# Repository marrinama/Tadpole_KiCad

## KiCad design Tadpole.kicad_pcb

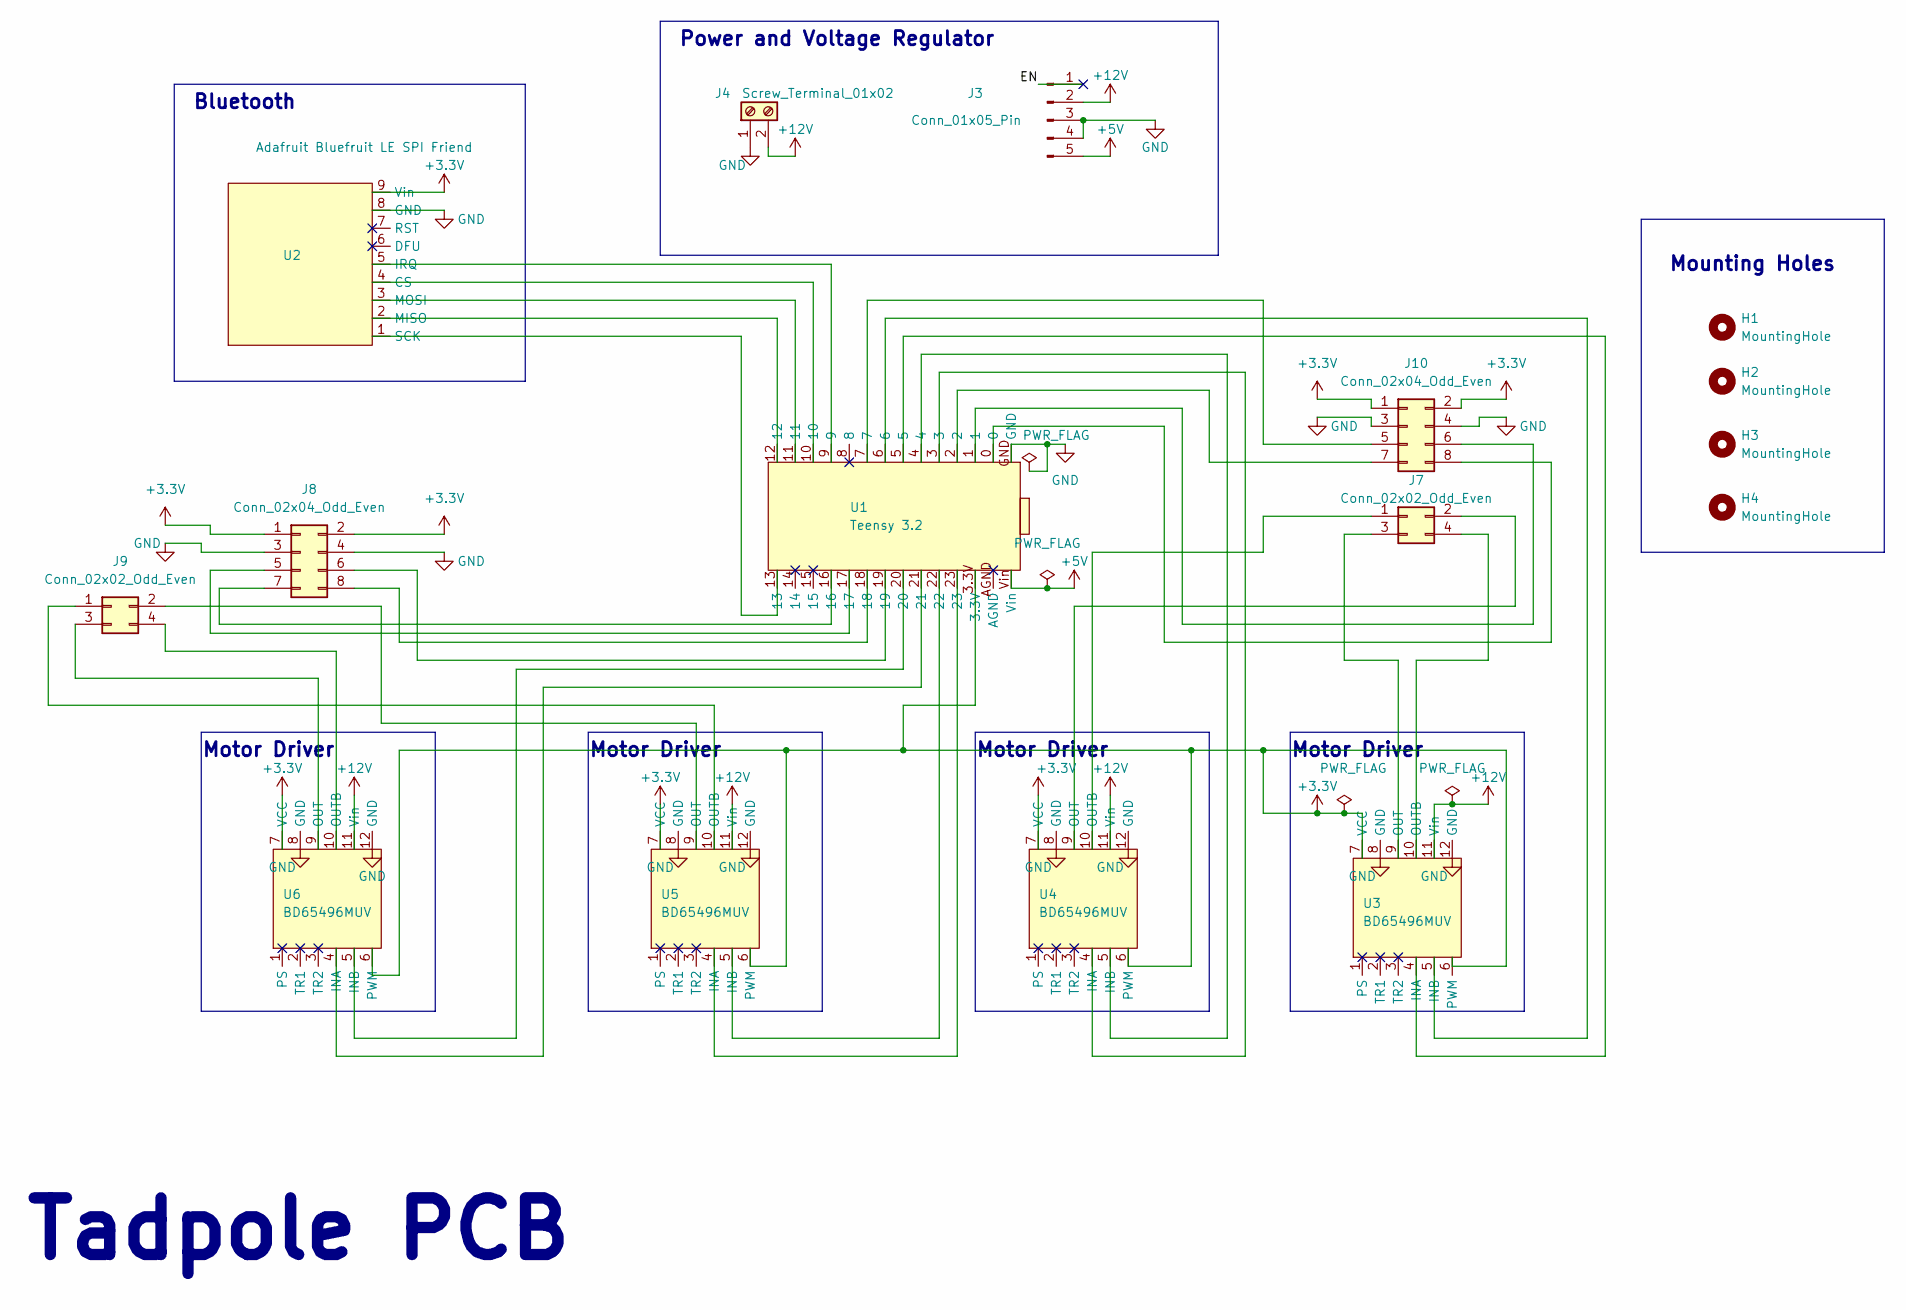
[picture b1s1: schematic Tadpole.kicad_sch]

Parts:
H1, H2, H3, H4: MountingHole; MountingHole_2.2mm_M2
J3: Conn_01x05_Pin; PinHeader_1x05_P2.54mm_Vertical
J4: Screw_Terminal_01x02; PinHeader_1x02_P2.54mm_Horizontal
J7, J9: Conn_02x02_Odd_Even; PinHeader_2x02_P2.54mm_Horizontal
J8, J10: Conn_02x04_Odd_Even; PinHeader_2x04_P2.54mm_Horizontal
U1: Teensy 3.2; teensy
U2: Adafruit Bluefruit LE SPI Friend
U3, U4, U5, U6: BD65496MUV

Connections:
+3.3V: J8.1, J8.2, J10.1, J10.2, U1.3.3V, U2.9 (Vin), U3.6 (PWM), U3.7 (VCC), U4.6 (PWM), U4.7 (VCC), U5.6 (PWM), U5.7 (VCC), U6.6 (PWM), U6.7 (VCC)
+5V: J3.5, U1.Vin
+12V: J3.2, J4.2, U3.11 (Vin), U4.11 (Vin), U5.11 (Vin), U6.11 (Vin)
/EN: J3.1
GND: J3.3, J3.4, J4.1, J8.3, J8.4, J10.3, J10.4, U1.GND, U2.8 (GND), U3.8 (GND), U3.12 (GND), U4.8 (GND), U4.12 (GND), U5.8 (GND), U5.12 (GND), U6.8 (GND), U6.12 (GND)
unnamed: J7.1, U4.10 (OUTB)
unnamed: J7.2, U4.9 (OUT)
unnamed: J7.3, U3.9 (OUT)
unnamed: J7.4, U3.10 (OUTB)
unnamed: J8.5, U1.17
unnamed: J8.6, U1.19
unnamed: J8.7, U1.16
unnamed: J8.8, U1.18
unnamed: J9.1, U5.10 (OUTB)
unnamed: J9.2, U5.9 (OUT)
unnamed: J9.3, U6.9 (OUT)
unnamed: J9.4, U6.10 (OUTB)
unnamed: J10.5, U1.7
unnamed: J10.6, U1.1
unnamed: J10.7, U1.2
unnamed: J10.8, U1.0
unnamed: U1.10, U2.4 (CS)
unnamed: U1.9, U2.5 (IRQ)
unnamed: U1.12, U2.2 (MISO)
unnamed: U1.11, U2.3 (MOSI)
unnamed: U1.13, U2.1 (SCK)
unnamed: U1.5, U3.4 (INA)
unnamed: U1.6, U3.5 (INB)
unnamed: U1.3, U4.4 (INA)
unnamed: U1.4, U4.5 (INB)
unnamed: U1.23, U5.4 (INA)
unnamed: U1.22, U5.5 (INB)
unnamed: U1.21, U6.4 (INA)
unnamed: U1.20, U6.5 (INB)

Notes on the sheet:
Bluetooth
Tadpole PCB
Motor Driver
Mounting Holes
Power and Voltage Regulator

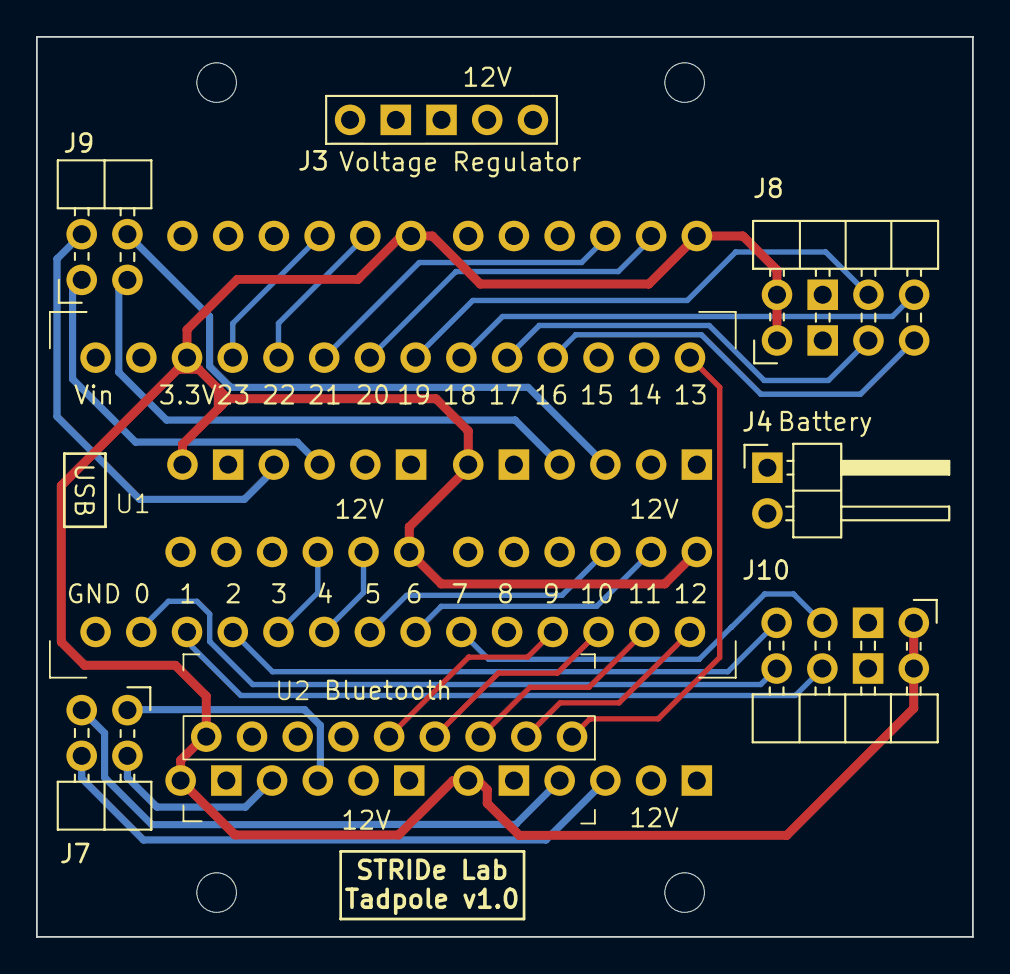
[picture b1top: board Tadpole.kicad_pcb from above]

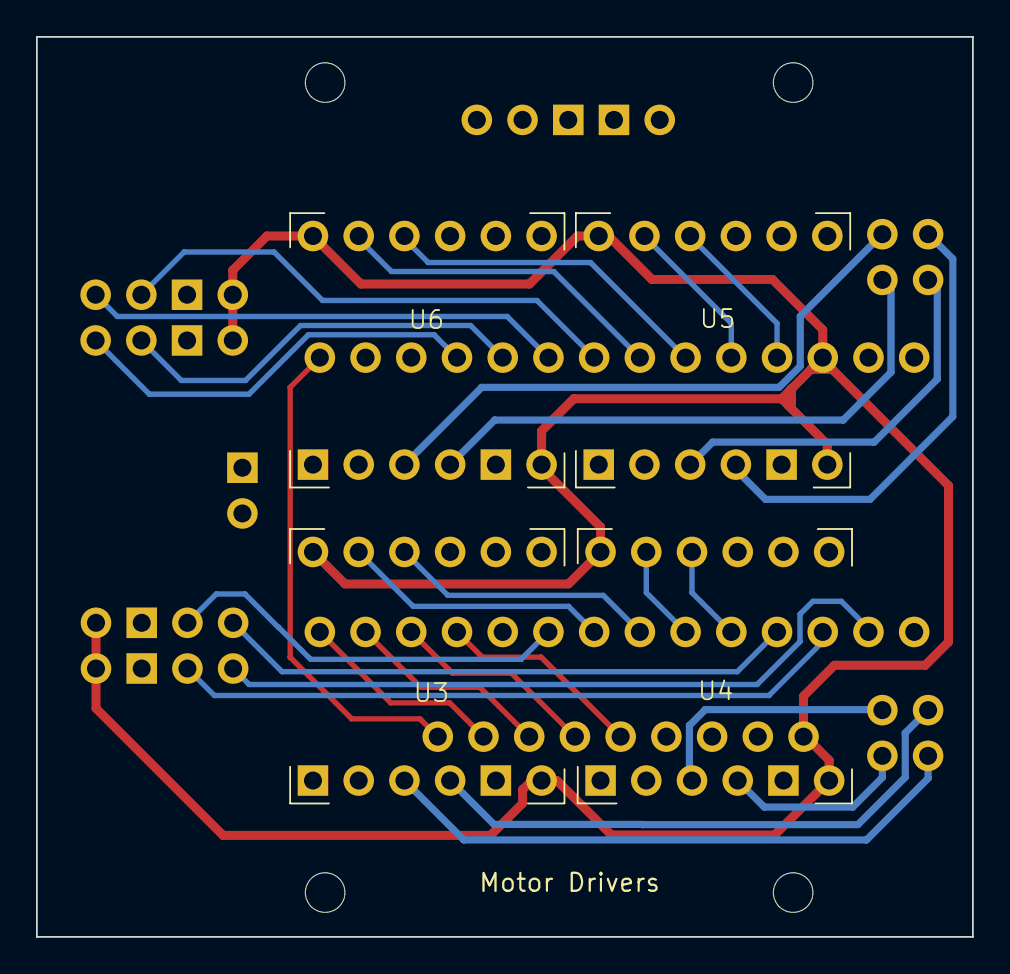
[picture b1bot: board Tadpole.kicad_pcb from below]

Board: 4 copper layers, 52.0 x 50.0 mm, 16 parts (4 on the bottom side), 33 nets.

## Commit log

2023-07-18 Create tadpole_gerber
